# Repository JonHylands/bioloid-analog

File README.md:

# bioloid-analog
A Bioloid device that provides an analog input

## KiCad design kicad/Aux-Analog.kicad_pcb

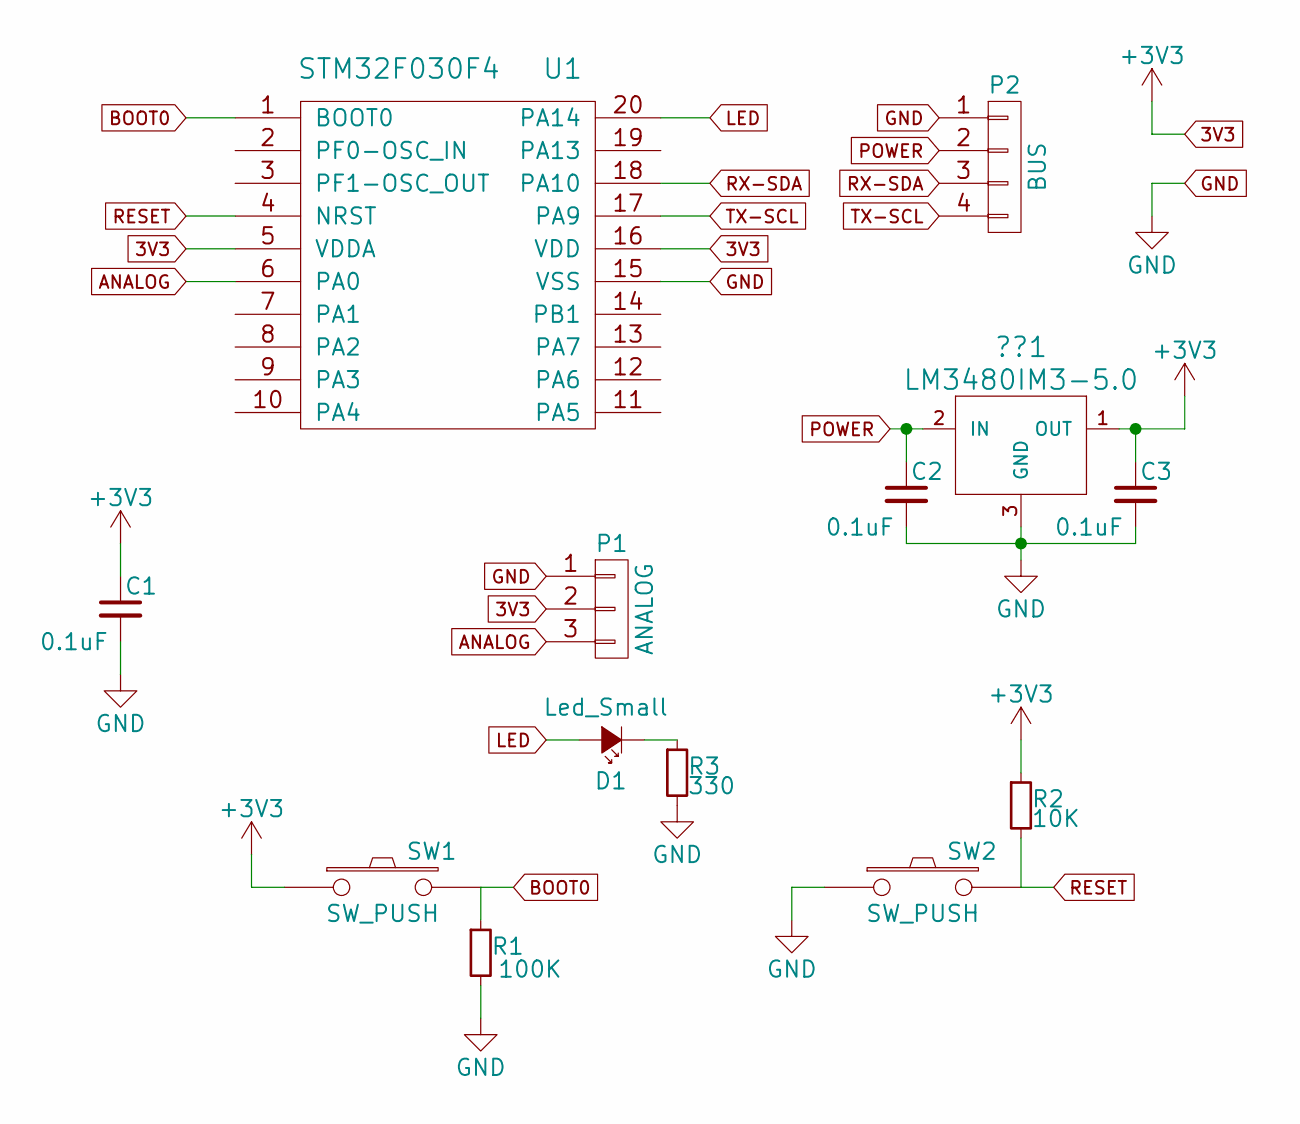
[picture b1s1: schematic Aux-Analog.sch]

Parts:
??1: LM3480IM3-5.0; SOT-23
C1, C2, C3: 0.1uF; C_0603
D1: Led_Small; LED_0603
P1: ANALOG; SIL_3_050_RA
P2: BUS; SIL_4_050_RA
R1: 100K; R_0603
R2: 10K; R_0603
R3: 330; R_0603
SW1, SW2: SW_PUSH; PUSH_SMT
U1: STM32F030F4; TSSOP-20_4.4x6.5mm_Pitch0.65mm

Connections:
3V3: ??1.1 (OUT), C1.1, C3.1, P1.2, R2.1, SW1.1, U1.5 (VDDA), U1.16 (VDD)
ANALOG: P1.3, U1.6 (PA0)
BOOT0: R1.1, SW1.2, U1.1 (BOOT0)
GND: ??1.3 (GND), C1.2, C2.2, C3.2, P1.1, P2.1, R1.2, R3.2, SW2.1, U1.15 (VSS)
LED: D1.2 (A), U1.20 (PA14)
unnamed: D1.1 (K), R3.1
POWER: ??1.2 (IN), C2.1, P2.2
RESET: R2.2, SW2.2, U1.4 (NRST)
RX-SDA: P2.3, U1.18 (PA10)
TX-SCL: P2.4, U1.17 (PA9)

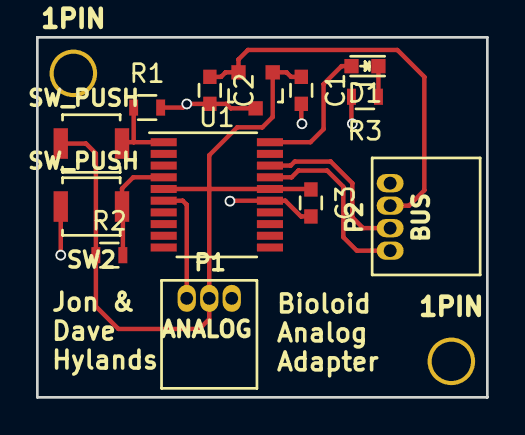
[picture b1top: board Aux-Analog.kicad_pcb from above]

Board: 2 copper layers, 25.0 x 20.0 mm, 15 parts (0 on the bottom side), 10 nets.

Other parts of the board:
1PIN, 1PIN#2: P***; 2_56_hole

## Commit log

2016-10-21 Initial push
